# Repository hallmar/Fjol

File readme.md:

# Fjöl 4-Voice Midi synth
# FIRMWARE AND HARDWARE STILL A WORK IN PROGRESS

Small demo video with non working LED's: https://www.youtube.com/watch?v=nTqA_WNiwQo

Current hardware uses the [Daisy Seed](https://www.electro-smith.com/daisy) platform from Electrosmith, which has 96kHz/24Bit stereo audio.

Fjöl is a 
4 voice polyphonic Phase modulation synthesizer. Using only sine waves you can get the same sounds as an FM synthesizer.

* digital ladder LPF with resonance
* usb A on the back to update firmware
* 3 operator Phase modulation with 3 algorithms(so far)
* two endless encoders with CV input for adjusting 8 different parameters 
* MIDI IN and MIDI THRU with type A midi minijacks as per MIDI standard.
* optional V/OCT and gate per voice expander also in the works

Encoder parameters are:

* stereo spread of voices(constant power)
* filter resonance
* filter envelope decay
* glide/portamento
* Operator 2 detune
* Operator 3 detune
* Operator 1 feedback (creates saw like wave)
* Operator 2 feedback

Potentiometers are:

* Operator 2 amplitude
* Operator 2 ratio
* Operator 3 amplitude
* Operator 3 ratio
* VCA Attack 
* VCA Release
* LPF frequency
* Filter envelope amplitude

Algorithms so far:

### Algo 1: 

OP2 -> OP1

OP3 -> OP1

### Algo 2:

OP3 -> OP2 -> OP1

### Algo 3:

OP3 -> OP1

OP2 -> OUT

## Where/how to order
It's all a work in progress.

~~Hopefully I'll have some beta testing units ready before summer 2023 :)~~

WELL that didn't work out. Putting this one on hiatus until I finalize the desktop version.
It's a struggle to work a full time job and try and work on this regularily.

## Designed With

* KiCAD
* Visual Studio Code(C++)
* Inkscape

## Versioning
* 1.0 - [Hardware] Original PCB
* 1.0 - [Software] Original software 
## Authors

* **Hallmar Gauti Halldórsson** - Fjöl Hardware and Firmware
* **Electrosmith** - libDaisy and DaisySP libraries

## License
Hardware: CC BY-SA 4.0

Software: CC BY-SA 4.0

But if you want to sell or do something with the software or hardware then it'd be nice to include my name and link to my Github somewhere :)

## Acknowledgments

* All of Mutable Instruments designs have been an insparation and a solid reference for both analog and digital circuits.
https://github.com/pichenettes/eurorack

* The whole idea of a 4 voice poly synth was planted in my head after trying MakeSynthsNotWar's String Theory module.
https://makesynthsnotwar.com/modules/stringtheory/

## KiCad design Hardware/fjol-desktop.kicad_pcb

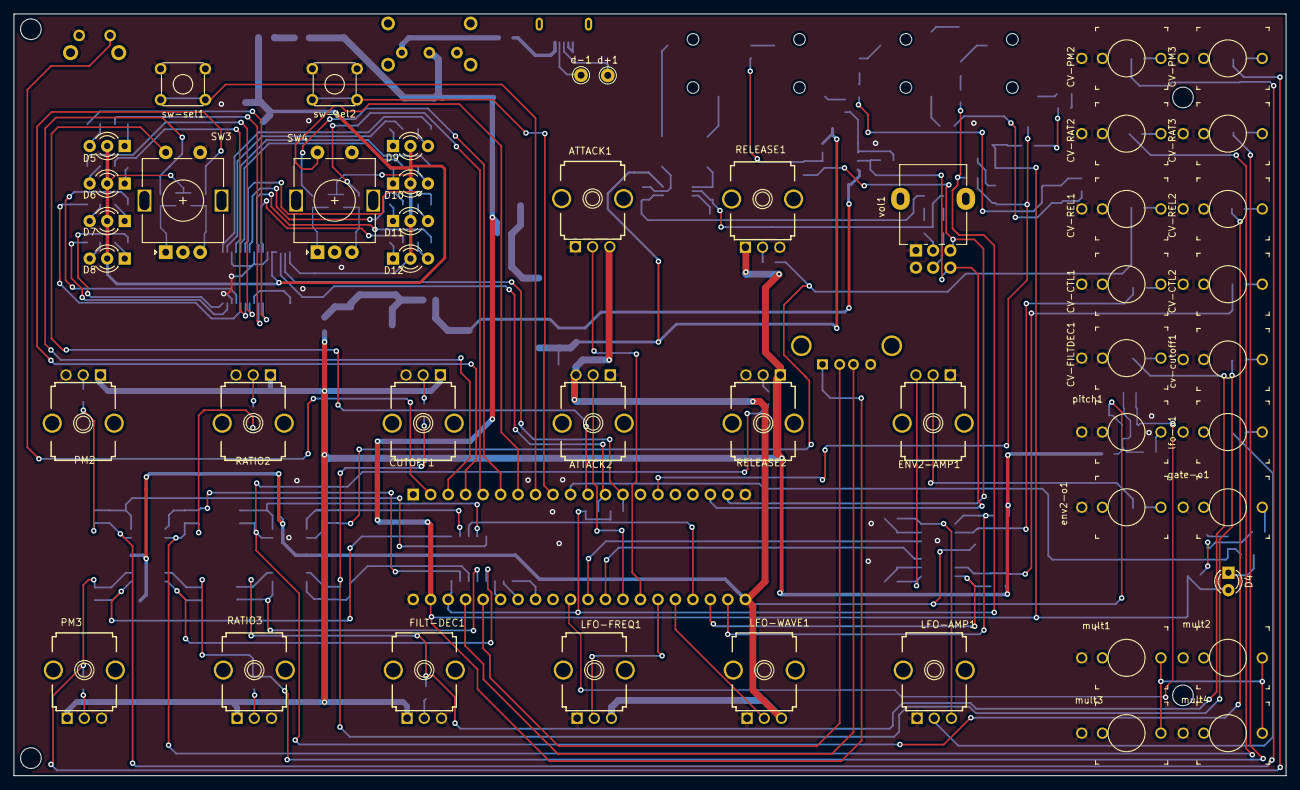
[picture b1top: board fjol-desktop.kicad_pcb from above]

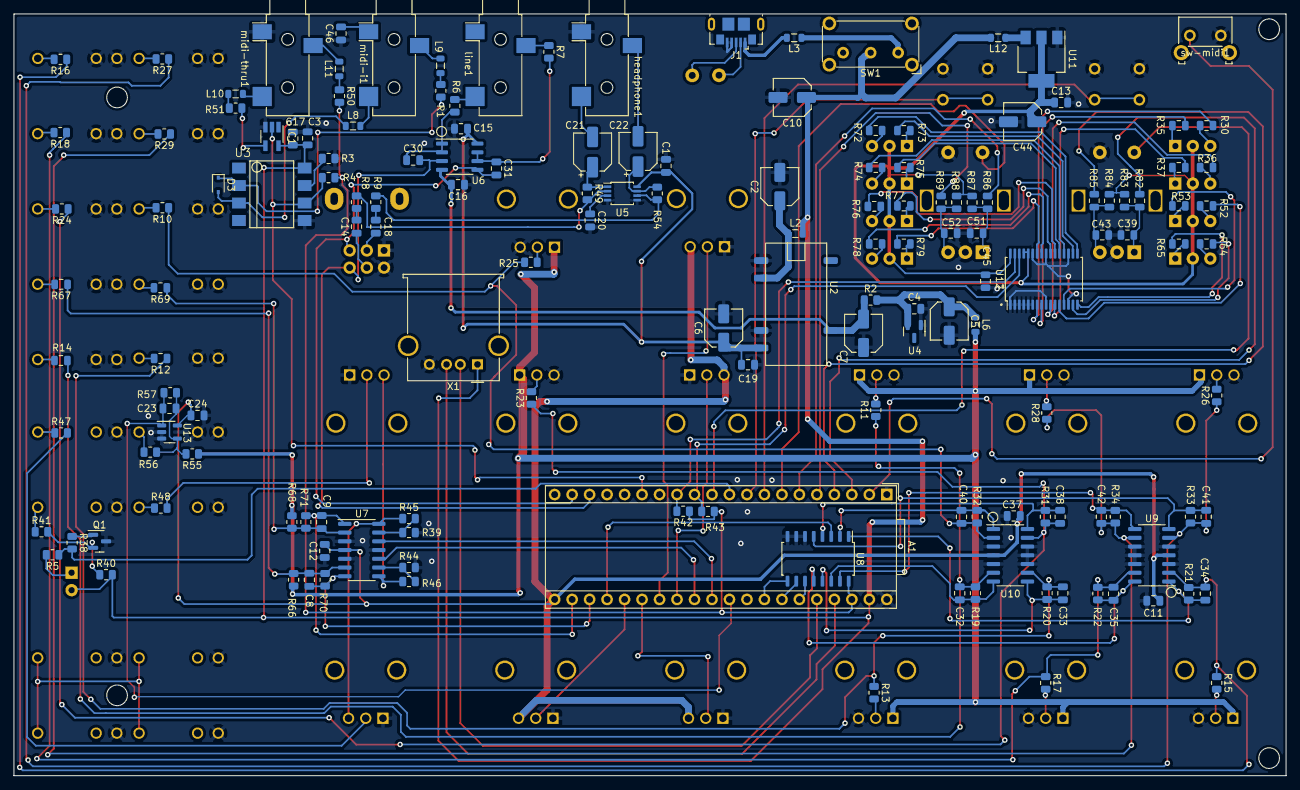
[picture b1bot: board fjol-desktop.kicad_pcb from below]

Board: 2 copper layers, 184.8 x 110.7 mm, 203 parts (155 on the bottom side), 159 nets.

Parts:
A1: Device_Audio_Electrosmith_Daisy_Seed_Rev4; Device_Audio_Electrosmith_Daisy_Seed
ATTACK1, ATTACK2: 50k-lin; 9MM_SNAP-IN_POT
C1, C3, C4, C11, C12, C13, C15, C16, C17, C19, C20, C24, C37, C39, C43, C45, C46, C51, C52: 100n; C_0805_2012Metric
C2, C6, C7, C10: 22u; C_Elec_5x5.8
C5, C44: 100u; C_Elec_5x5.8
C8, C9, C23, C32, C33, C34, C35, C38, C40, C41, C42: 1n; C_0805_2012Metric
C14, C18: 470n; C_0805_2012Metric
C21, C22: 220u; CP_Elec_5x5.8
C30, C31: 100p; C_0805_2012Metric
CUTOFF1: 50k-lin; 9MM_SNAP-IN_POT
CV-CTL1, CV-CTL2: THONKICONNNEW; WQP-PJ301M-12_JACK
CV-FILTDEC1: THONKICONNNEW; WQP-PJ301M-12_JACK
CV-PM2, CV-PM3: THONKICONNNEW; WQP-PJ301M-12_JACK
CV-RAT2, CV-RAT3: THONKICONNNEW; WQP-PJ301M-12_JACK
CV-REL1, CV-REL2: THONKICONNNEW; WQP-PJ301M-12_JACK
D3: 1N4148; D_SOD-323
D4: LED; LED_D3.0mm_FlatTop
D5, D6, D7, D8, D9, D10, D11, D12: LED_Dual_KAK; LED_D3.0mm-3
ENV2-AMP1: 50k-lin; 9MM_SNAP-IN_POT
FILT-DEC1: 50k-lin; 9MM_SNAP-IN_POT
IC1: 741G17DBV; SOT-23-5_HandSoldering
J1: USB_B; USB_Micro-B_GCT_USB3076-30-A
L2, L3, L12: 2.2u; L_0805_2012Metric
L6: 33u; L_0805_2012Metric
L8, L9, L10, L11: BLM21AG102SN1D; L_0805_2012Metric
LFO-AMP1: 50k-lin; 9MM_SNAP-IN_POT
LFO-FREQ1: 50k-lin; 9MM_SNAP-IN_POT
LFO-WAVE1: 50k-lin; 9MM_SNAP-IN_POT
PM2, PM3: 50k-lin; 9MM_SNAP-IN_POT
Q1: BC847; SOT-23
R1: 220; R_0805_2012Metric
R2, R3, R5, R6, R7, R38, R41: 1k; R_0805_2012Metric
R4: 470; R_0805_2012Metric
R8, R9: 22k; R_0805_2012Metric
R10, R12, R14, R16, R18, R24, R27, R29, R45, R46, R67, R69: 100k; R_0805_2012Metric
R11, R13, R15, R17, R23, R25, R26, R28, R39, R44, R66, R68: 200k; R_0805_2012Metric
R19, R20, R21, R22, R31, R32, R33, R34, R70, R71: 66.5k; R_0805_2012Metric
R30, R35, R36, R37, R47, R48, R52, R53, R64, R65, R72, R73, R74, R75, R76, R77, R78, R79: 100; R_0805_2012Metric
R40, R42, R43, R82, R83, R84, R85, R86, R87, R88, R89: 10k; R_0805_2012Metric
R49, R54: 33k; R_0805_2012Metric
R50: 33; R_0805_2012Metric
R51: 10; R_0805_2012Metric
R55: 140k 1%; R_0805_2012Metric
R56: 100k 1%; R_0805_2012Metric
R57: 33k 1%; R_0805_2012Metric
RATIO2, RATIO3: 50k-lin; 9MM_SNAP-IN_POT
RELEASE1, RELEASE2: 50k-lin; 9MM_SNAP-IN_POT
SW1: SW_SPST; SW_E-Switch_EG1224_SPDT_Angled
SW3: ctl1; RotaryEncoder_Alps_EC11E-Switch_Vertical_H20mm
SW4: ctl2; RotaryEncoder_Alps_EC11E-Switch_Vertical_H20mm
U2: PESE1-S5-D12-M-TR; PESE1
U3: 6N138; DIL8-SMD
U4: LM4040DBZ-10; SOT-23
U5: LM4810; TSSOP-8_3x3mm_P0.65mm
U6: TL072; SO-8_3.9x4.9mm_P1.27mm
U7, U9, U10: MCP6004; SOIC-14_3.9x8.7mm_P1.27mm
U8: 74HC4051D; SOIC-16_4.55x10.3mm_P1.27mm
U11: NCP1117-3.3_SOT223; SOT-223-3_TabPin2
U12: PCA9622; TSSOP-32_6.1x11mm_P0.65mm
U13: MCP6001-OT; SOT-23-5
X1: KUSBVX; USB_A_Molex_67643_Horizontal
cv-cutoff1: THONKICONNNEW; WQP-PJ301M-12_JACK
d+1: TestPoint; Pin_D1.0mm_L10.0mm
d-1: TestPoint; Pin_D1.0mm_L10.0mm
env2-o1: THONKICONNNEW; WQP-PJ301M-12_JACK
gate-o1: THONKICONNNEW; WQP-PJ301M-12_JACK
headphone1: AudioJack3; Jack_3.5mm_CUI_SJ-3523-SMT_Horizontal
lfo-o1: THONKICONNNEW; WQP-PJ301M-12_JACK
line1: AudioJack3; Jack_3.5mm_CUI_SJ-3523-SMT_Horizontal
midi-i1: AudioJack3; Jack_3.5mm_CUI_SJ-3523-SMT_Horizontal
midi-thru1: AudioJack3; Jack_3.5mm_CUI_SJ-3523-SMT_Horizontal
mult1, mult2, mult3, mult4: THONKICONNNEW; WQP-PJ301M-12_JACK
pitch1: THONKICONNNEW; WQP-PJ301M-12_JACK
sw-midi1: SW_Push; SW_Tactile_SKHH_Angled
sw-sel1, sw-sel2: SW_MEC_5G; SW_TH_Tactile_Omron_B3F-10xx
vol1: R_Potentiometer_Dual; Potentiometer_Alpha_RD902F-40-00D_Dual_Vertical

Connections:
+3.3V: A1.38 (3V3_D), R4.2, R42.1, R43.2, R50.2, U8.16 (VDD)
+3.3VA: A1.21 (3V3_A), ATTACK1.3, ATTACK2.3, C11.2, C12.2, C24.1, C37.2, LFO-FREQ1.3, LFO-WAVE1.3, U7.4 (V+), U9.4 (V+), U10.4 (V+), U13.5 (V+)
+3.3VP: C13.1, C44.1, C45.1, D5.2 (A), D6.2 (A), D7.2 (A), D8.2 (A), D9.2 (A), D10.2 (A), D11.2 (A), D12.2 (A), R83.2, R84.2, R87.2, R88.2, U11.2 (VO), U12.28 (A5), U12.29 (A6), U12.32 (VDD)
+5V: A1.39 (VIN), C3.1, C10.1, C17.1, D4.2 (A), IC1.5 (VCC), L2.2, L12.2, R40.2, SW1.2 (B), U3.8 (VCC), X1.1
+12V: C1.1, C6.1, C15.1, C19.1, U2.5 (-VOUT), U5.8 (VDD), U6.8 (V+)
-10V: CUTOFF1.1, FILT-DEC1.1, L6.2, PM2.1, PM3.1, R55.1, R66.2, R68.2, RATIO2.1, RATIO3.1, RELEASE1.1, RELEASE2.1
-12V: C7.2, C16.2, R2.1, U2.7 (+VOUT), U6.4 (V-)
A: A1.35 (SAI2_SCK_B), U8.11 (A)
ATTACK1: A1.27 (ADC_INP11), ATTACK1.2
ATTACK2: A1.28 (ADC1_INP4), ATTACK2.2
B: A1.34 (SAI2_FS_B), U8.10 (B)
C: A1.33 (SAI2_SD_A), U8.9 (C)
CONTROL1_CV: A1.22 (ADC_INP10), C9.1, R71.1, U7.1
CONTROL2_CV: A1.23 (ADC_INP15), C8.1, R70.1, U7.7
CONTROL3: C33.1, R20.1, U8.13 (X0), U10.8
D+: A1.37 (USB_HS_D_+), X1.3
D-: A1.36 (USB_HS_D_-), X1.2
GATE: A1.10 (SPI1_MISO), R5.1, R38.2
GND: A1.1 (USB_HS_ID), A1.20 (AGND), A1.40 (GND), ATTACK1.1, ATTACK2.1, C1.2, C2.2, C3.2, C4.2, C5.2, C6.2, C7.1, C10.2, C11.1, C12.1, C13.2, C15.2, C16.1, C17.2, C19.2, C20.2, C24.2, C37.1, C39.1, C43.1, C44.2, C45.2, C46.1, C51.1, C52.1, CUTOFF1.3, CV-CTL1.P$2_SWITCH (SWITCH), CV-CTL1.P$3_SLEEVE (SLEEVE), CV-CTL2.P$2_SWITCH (SWITCH), CV-CTL2.P$3_SLEEVE (SLEEVE), CV-FILTDEC1.P$2_SWITCH (SWITCH), CV-FILTDEC1.P$3_SLEEVE (SLEEVE), CV-PM2.P$2_SWITCH (SWITCH), CV-PM2.P$3_SLEEVE (SLEEVE), CV-PM3.P$2_SWITCH (SWITCH), CV-PM3.P$3_SLEEVE (SLEEVE), CV-RAT2.P$2_SWITCH (SWITCH), CV-RAT2.P$3_SLEEVE (SLEEVE), CV-RAT3.P$2_SWITCH (SWITCH), CV-RAT3.P$3_SLEEVE (SLEEVE), CV-REL1.P$2_SWITCH (SWITCH), CV-REL1.P$3_SLEEVE (SLEEVE), CV-REL2.P$2_SWITCH (SWITCH), CV-REL2.P$3_SLEEVE (SLEEVE), ENV2-AMP1.1, FILT-DEC1.3, IC1.3 (GND), J1.4 (GND), J1.5 (Shield), LFO-AMP1.1, LFO-FREQ1.1, LFO-WAVE1.1, PM2.3, PM3.3, Q1.3 (E), R3.1, R39.2, R44.2, RATIO2.3, RATIO3.3, RELEASE1.3, RELEASE2.3, SW3.C, SW3.S1, SW4.C, SW4.S1, U2.1 (GND), U2.4 (0V), U3.5 (GND), U4.1 (K), U5.4 (GND), U5.5 (SHDN), U7.3 (+), U7.5 (+), U7.11 (V-), U8.6 (Inh), U8.7 (VEE), U8.8 (VSS), U9.3 (+), U9.5 (+), U9.10 (+), U9.11 (V-), U9.12 (+), U10.3 (+), U10.5 (+), U10.10 (+), U10.11 (V-), U10.12 (+), U11.1 (GND), U12.1 (VSS), U12.2 (A0), U12.3 (A1), U12.4 (A2), U12.5 (A3), U12.6 (A4), U12.9 (VSS), U12.14 (VSS), U12.19 (VSS), U12.24 (VSS), U12.27 (!OE), U13.2 (V-), U13.3 (+), X1.4, cv-cutoff1.P$2_SWITCH (SWITCH), cv-cutoff1.P$3_SLEEVE (SLEEVE), env2-o1.P$3_SLEEVE (SLEEVE), gate-o1.P$3_SLEEVE (SLEEVE), headphone1.S, lfo-o1.P$3_SLEEVE (SLEEVE), midi-thru1.S, mult1.P$3_SLEEVE (SLEEVE), mult2.P$3_SLEEVE (SLEEVE), mult3.P$3_SLEEVE (SLEEVE), mult4.P$3_SLEEVE (SLEEVE), pitch1.P$2_SWITCH (SWITCH), pitch1.P$3_SLEEVE (SLEEVE), sw-midi1.2, sw-sel1.3 (B), sw-sel1.4 (B), sw-sel2.3 (B), sw-sel2.4 (B), vol1.1, vol1.4
LFO-FREQ: A1.26 (ADC_INP3), LFO-FREQ1.2
LFO-WAVE: A1.25 (ADC_INP7), LFO-WAVE1.2
MIDI-RX: A1.15 (USART1_RX), IC1.2 (I), R4.1, U3.6 (VO2)
MIDI-RX4: L9.1, R1.2
MIDI-RX5: D3.2 (A), L8.1, U3.3 (C2)
MIDI-THRU: IC1.4 (O), R51.2
unnamed: C2.1, L2.1, U2.2 (VIN)
unnamed: C4.1, C5.1, L6.1, R2.2, U4.2 (A)
unnamed: C8.2, R66.1, R67.1, R70.2, U7.6 (-)
unnamed: C9.2, R68.1, R69.1, R71.2, U7.2 (-)
unnamed: C14.1, vol1.5
unnamed: C14.2, R8.2
unnamed: C18.1, vol1.2
unnamed: C18.2, R9.2
unnamed: C20.1, U5.3 (BYPASS)
unnamed: C21.1, R49.1, U5.1 (VOUT1)
unnamed: C21.2, headphone1.T
unnamed: C22.1, R54.1, U5.7 (VOUT2)
unnamed: C22.2, headphone1.R
unnamed: C23.2, R55.2, R56.2, R57.1, U13.4 (-)
unnamed: C30.1, R6.2, U6.1, U6.2 (-)
unnamed: C31.1, R7.2, U6.6 (-), U6.7
unnamed: C32.2, R11.1, R14.1, R19.2, U10.6 (-)
unnamed: C33.2, R12.1, R13.1, R20.2, U10.9 (-)
unnamed: C34.2, R15.1, R16.1, R21.2, U9.2 (-)
unnamed: C35.2, R17.1, R18.1, R22.2, U9.13 (-)
unnamed: C38.2, R23.1, R24.1, R31.2, U10.13 (-)
unnamed: C39.2, R82.1, R83.1, SW3.A
unnamed: C40.2, R10.1, R25.1, R32.2, U10.2 (-)
unnamed: C41.2, R26.1, R27.1, R33.2, U9.6 (-)
unnamed: C42.2, R28.1, R29.1, R34.2, U9.9 (-)
unnamed: C43.2, R84.1, R85.2, SW3.B
unnamed: C46.2, midi-i1.S
unnamed: C51.2, R86.1, R87.1, SW4.A
unnamed: C52.2, R88.1, R89.2, SW4.B
unnamed: CUTOFF1.2, R11.2
unnamed: CV-CTL1.P$1_TIP (TIP), R69.2
unnamed: CV-CTL2.P$1_TIP (TIP), R67.2
unnamed: CV-FILTDEC1.P$1_TIP (TIP), R12.2
unnamed: CV-PM2.P$1_TIP (TIP), R27.2
unnamed: CV-PM3.P$1_TIP (TIP), R16.2
unnamed: CV-RAT2.P$1_TIP (TIP), R29.2
unnamed: CV-RAT3.P$1_TIP (TIP), R18.2
unnamed: CV-REL1.P$1_TIP (TIP), R10.2
unnamed: CV-REL2.P$1_TIP (TIP), R24.2
unnamed: D3.1 (K), R1.1, U3.2 (C1)
unnamed: D4.1 (K), R5.2
unnamed: D5.1 (K1), R35.1
unnamed: D5.3 (K2), R30.1
unnamed: D6.1 (K1), R37.1
unnamed: D6.3 (K2), R36.1
unnamed: D7.1 (K1), R53.1
unnamed: D7.3 (K2), R52.1
unnamed: D8.1 (K1), R65.1
unnamed: D8.3 (K2), R64.1
unnamed: D9.1 (K1), R73.1
unnamed: D9.3 (K2), R72.1
unnamed: D10.1 (K1), R75.1
unnamed: D10.3 (K2), R74.1
unnamed: D11.1 (K1), R77.1
unnamed: D11.3 (K2), R76.1
unnamed: D12.1 (K1), R79.1
unnamed: D12.3 (K2), R78.1
unnamed: ENV2-AMP1.2, R48.2
unnamed: ENV2-AMP1.3, R46.1, U7.8
unnamed: FILT-DEC1.2, R13.2
unnamed: J1.1 (VBUS), L3.2
unnamed: J1.2 (D-), d-1.1
unnamed: J1.3 (D+), d+1.1
unnamed: L3.1, SW1.1 (A)
unnamed: L8.2, midi-i1.T
unnamed: L9.2, midi-i1.R
unnamed: L10.1, R51.1
unnamed: L10.2, midi-thru1.T
unnamed: L11.1, R50.1
unnamed: L11.2, midi-thru1.R
unnamed: L12.1, U11.3 (VI)
unnamed: LFO-AMP1.2, R47.2
unnamed: LFO-AMP1.3, R45.1, U7.14
unnamed: PM2.2, R26.2
unnamed: PM3.2, R15.2
unnamed: Q1.1 (B), R38.1
unnamed: Q1.2 (C), R40.1, R41.2
unnamed: R3.2, U3.7 (VO1)
unnamed: R6.1, line1.T
unnamed: R7.1, line1.R
unnamed: R14.2, cv-cutoff1.P$1_TIP (TIP)
unnamed: R17.2, RATIO3.2
unnamed: R23.2, RELEASE2.2
unnamed: R25.2, RELEASE1.2
unnamed: R28.2, RATIO2.2
unnamed: R39.1, R45.2, U7.13 (-)
unnamed: R41.1, gate-o1.P$1_TIP (TIP)
unnamed: R44.1, R46.2, U7.9 (-)
unnamed: R47.1, lfo-o1.P$1_TIP (TIP)
unnamed: R48.1, env2-o1.P$1_TIP (TIP)
unnamed: R8.1, R49.2, U5.2 (VIN1)
unnamed: R9.1, R54.2, U5.6 (VIN2)
unnamed: R56.1, pitch1.P$1_TIP (TIP)
unnamed: mult1.P$1_TIP (TIP), mult2.P$1_TIP (TIP), mult3.P$1_TIP (TIP), mult4.P$1_TIP (TIP)
PM2: C41.1, R33.1, U8.5 (X5), U9.7
PM3: C34.1, R21.1, U8.1 (X4), U9.1
RATIO2: C42.1, R34.1, U8.15 (X2), U9.8
RATIO3: C35.1, R22.1, U8.12 (X3), U9.14
RELEASE1: C40.1, R32.1, U8.2 (X6), U10.1
RELEASE2: C38.1, R31.1, U8.4 (X7), U10.14
SCL: A1.12 (I2C1_SCL), R43.1, U12.30 (SCL)
SDA: A1.13 (I2C1_SDA), R42.2, U12.31 (SDA)
controls: A1.24 (ADC_INP5), U8.3 (X)
ctl1_enc_A: A1.3 (SDMMC1_D2), R82.2
ctl1_enc_B: A1.4 (SDMMC1_D1), R85.1
ctl1_sw: A1.11 (SPI1_MOSI), SW3.S2
ctl2_enc_A: A1.6 (SDMMC1_CMD), R86.2
ctl2_enc_B: A1.5 (SDMMC1_D0), R89.1
ctl2_sw: A1.7 (SDMMC1_CK), SW4.S2
cutoff: C32.1, R19.1, U8.14 (X1), U10.7
dac1: A1.29 (DAC1_OUT2), U7.10 (+)
dac2: A1.30 (DAC1_OUT1), U7.12 (+)
dac_left: A1.18 (AUDIO_OUT_L), C30.2, U6.3 (+), vol1.6
dac_right: A1.19 (AUDIO_OUT_R), C31.2, U6.5 (+), vol1.3
led1_g: R30.2, U12.7 (LED0)
led1_r: R35.2, U12.8 (LED1)
led2_g: R36.2, U12.10 (LED2)
led2_r: R37.2, U12.11 (LED3)
led3_g: R52.2, U12.12 (LED4)
led3_r: R53.2, U12.13 (LED5)
led4_g: R64.2, U12.15 (LED6)
led4_r: R65.2, U12.16 (LED7)
led5_g: R72.2, U12.17 (LED8)
led5_r: R73.2, U12.18 (LED9)
led6_g: R74.2, U12.20 (LED10)
led6_r: R75.2, U12.21 (LED11)
led7_g: R76.2, U12.22 (LED12)
led7_r: R77.2, U12.23 (LED13)
led8_g: R78.2, U12.25 (LED14)
led8_r: R79.2, U12.26 (LED15)
midi_sw: A1.2 (SDMMC1_D3), sw-midi1.1
switch1_sw: A1.8 (SPI1_NSS), sw-sel1.1 (A), sw-sel1.2 (A)
switch2_sw: A1.9 (SPI1_SCK), sw-sel2.1 (A), sw-sel2.2 (A)
voct: A1.31 (SAI2_MCLK_B), C23.1, R57.2, U13.1

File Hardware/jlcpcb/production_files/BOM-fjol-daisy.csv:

Comment,Designator,Footprint,LCSC
22u,"C10,C6,C7",C_Elec_5x5.8,C128468
LM4040DBZ-10,U4,SOT-23,C129969
100k 1%,"R10,R12,R14,R16,R18,R24,R27,R29,R44,R45,R46,R61,R63,R67,R69",R_0805_2012Metric,C149504
Conn_02x05_Odd_Even,J2,PinHeader_2x05_P1.27mm_Vertical_SMD,C150517
741G17DBV,IC1,SOT-23-5_HandSoldering,C151394
STPS1L30U,"D1,D2",D_SMB,C157388
100,"R30,R35,R36,R37,R52,R53,R64,R65,R72,R73,R74,R75,R76,R77,R78,R79",R_0805_2012Metric,C17408
10k,"R40,R42,R43,R48,R49,R58,R59,R82,R83,R84,R85,R86,R87,R88,R89",R_0805_2012Metric,C17414
10,R51,R_0805_2012Metric,C17415
140k 1%,"R47,R60,R62,R9",R_0805_2012Metric,C17460
1k,"R2,R3,R38,R41,R5,R54,R55",R_0805_2012Metric,C17513
200k,"R11,R13,R15,R17,R23,R25,R26,R28,R66,R68",R_0805_2012Metric,C17539
220,R1,R_0805_2012Metric,C17557
33k 1%,"R56,R57,R80,R81",R_0805_2012Metric,C17633
33,R50,R_0805_2012Metric,C17634
470,R4,R_0805_2012Metric,C17710
47k,"R7,R8",R_0805_2012Metric,C17713
66.5k,"R19,R20,R21,R22,R31,R32,R33,R34,R70,R71",R_0805_2012Metric,C17791
100p,"C30,C31",C_0805_2012Metric,C1790
Conn_01x16_Male,J7,PinHeader_2x08_P2.54mm_Vertical_SMD,C188235
BC847,"Q1,Q2,Q3,Q4,Q5",SOT-23,C2138
6N138,U3,DIL8-SMD,C255744
Conn_01x10_Female,"J10,J6",PinSocket_2x05_P2.54mm_Vertical_SMD,C261072
NCP1117-3.3_SOT223,"U11,U2",SOT-223-3_TabPin2,C26537
PCA9622,U12,TSSOP-32_6.1x11mm_P0.65mm,C2678561
100u,"C2,C44,C5",C_Elec_5x5.8,C336761
Conn_01x16_Female,J8,PinSocket_2x08_P2.54mm_Vertical_SMD,C3975153
33u,"L12,L2,L6",L_0805_2012Metric,C404761
1n,"C20,C21,C22,C23,C32,C33,C34,C35,C38,C40,C41,C42,C8,C9",C_0805_2012Metric,C46653
100n,"C1,C11,C13,C15,C16,C17,C19,C24,C3,C36,C37,C39,C4,C43,C45,C46,C51,C52",C_0805_2012Metric,C49678
TL072,U6,SO-8_3.9x4.9mm_P1.27mm,C6961
MCP6002,U13,SOIC-8-1EP_3.9x4.9mm_P1.27mm_EP2.514x3.2mm,C7377
MCP6004,"U10,U7,U9",SOIC-14_3.9x8.7mm_P1.27mm,C7378
BLM21AG102SN1D,"L10,L11,L4,L5,L7,L8,L9",L_0805_2012Metric,C85835
Conn_01x18_Male,J5,PinHeader_2x09_P2.54mm_Vertical_SMD,C88175
Conn_01x18_Female,J9,PinSocket_2x09_P2.54mm_Vertical_SMD,C920936
74HC4051D,U8,SOIC-16_4.55x10.3mm_P1.27mm,C9386
33u,L1,L_1206_3216Metric,
1N4148,D3,D_0805_2012Metric,
PESE1,U1,PESE1,
50k-lin,ATTACK1,9MM_SNAP-IN_POT,
50k-lin,cutoff1,9MM_SNAP-IN_POT,
50k-lin,RELEASE1,9MM_SNAP-IN_POT,
50k-lin,CTL2,9MM_SNAP-IN_POT,
Conn_02x08_Odd_Even,J1,con-3m-PAK100_2500-16,
ctl1,SW3,RotaryEncoder_Alps_EC11E-Switch_Vertical_H20mm,
ctl2,SW4,RotaryEncoder_Alps_EC11E-Switch_Vertical_H20mm,
LED_Dual_KAK,D5,LED_D3.0mm-3,
LED_Dual_KAK,D6,LED_D3.0mm-3,
LED_Dual_KAK,D7,LED_D3.0mm-3,
LED_Dual_KAK,D8,LED_D3.0mm-3,
LED_Dual_KAK,D9,LED_D3.0mm-3,
LED_Dual_KAK,D10,LED_D3.0mm-3,
LED_Dual_KAK,D11,LED_D3.0mm-3,
LED_Dual_KAK,D12,LED_D3.0mm-3,
50k-lin,PM2,9MM_SNAP-IN_POT,
50k-lin,RATIO1,9MM_SNAP-IN_POT,
50k-lin,RATIO2,9MM_SNAP-IN_POT,
50k-lin,PM1,9MM_SNAP-IN_POT,
Device_Audio_Electrosmith_Daisy_Seed_Rev4,A1,Device_Audio_Electrosmith_Daisy_Seed,
KUSBVX,X1,USB_A_Molex_67643_Horizontal,
LED,D4,LED_D3.0mm,

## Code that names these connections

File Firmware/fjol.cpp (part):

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  uint8_t knob_mapping[8] = {4,2,5,3,7,6,1,0};
  float callbackrate = hw.AudioCallbackRate();
  //how the fuck does this init work?? what object does it want??
  // gate[0].gate.Init(&(hw.GetPin(gate1_pin)));
  // gate[1].gate.Init(&(hw.GetPin(gate2_pin)));
  // gate[2].gate.Init(&(hw.GetPin(gate3_pin)));
  // gate[3].gate.Init(&(hw.GetPin(gate4_pin)));

  sw2.Init(hw.GetPin(sw2_pin),callbackrate);
  sw1.Init(hw.GetPin(sw1_pin),callbackrate);
  midi_sw.Init(hw.GetPin(midi_sw_pin),callbackrate);

  enc[0].enc.Init(hw.GetPin(ctl1_enc_a_pin),hw.GetPin(ctl1_enc_b_pin),hw.GetPin(ctl1_sw_pin),callbackrate);
  enc[1].enc.Init(hw.GetPin(ctl2_enc_a_pin),hw.GetPin(ctl2_enc_b_pin),hw.GetPin(ctl2_sw_pin),callbackrate);

  for(int i = 0; i<8; i++)
  {
    if(i<2){cv[i].input.Init(hw.adc.GetPtr(i),callbackrate,false,true,0.002);}
    controls[i].input.Init(hw.adc.GetMuxPtr(2,knob_mapping[i]),callbackrate,false,true,0.002);
    
  }
  for(int i=3;i<7;i++)
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
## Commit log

2023-01-17 upload daisy version of fjöl
2023-01-19 upload firmware
2023-01-19 update makefile and file cleanup
2023-01-22 new build
2023-02-11 upload everything
2023-02-11 update frontpanel
